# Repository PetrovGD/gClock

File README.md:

# gClock -- Simple and Reliable

### gClock is a simple alarm clock, powered by an ESP32C3. It features functions as:

* Setting an alarm
* Removing an alarm
* Setting minutes until the alarm
* more in future versions

## Bill of Materials (BOM)
 - 4pcs Cherry MX Switches
 - 4pcs Keycaps of your choice
 - 1pcs 3.3V buzzer
 - 1pcs Seeed Studio ESP32C3
 - 1pcs SSD1306 128x64 0.91inch display (I will source the screen myself and won't use the one in the Blare kit)
 - 1pcs 3D printed custom enclosure (containing a main part and a protective cover which is going to be glued to the main part)
 - 2pcs M3x8mm Screws
 - 4pcs M3x16mm Screws (For securing the top plate to the main part)
## Plans to upgrade
* Add a functionality for the user to choose a melody
* Add a snooze and stop alarm functions (now it just rings for set amount of seconds)
* Make a more futuristic design
## Screenshots of the project
### PCB design

### Schematic

### Top Part

### Bottom Part

### Main Menu

### Set alarm Menu

### Set minutes Menu

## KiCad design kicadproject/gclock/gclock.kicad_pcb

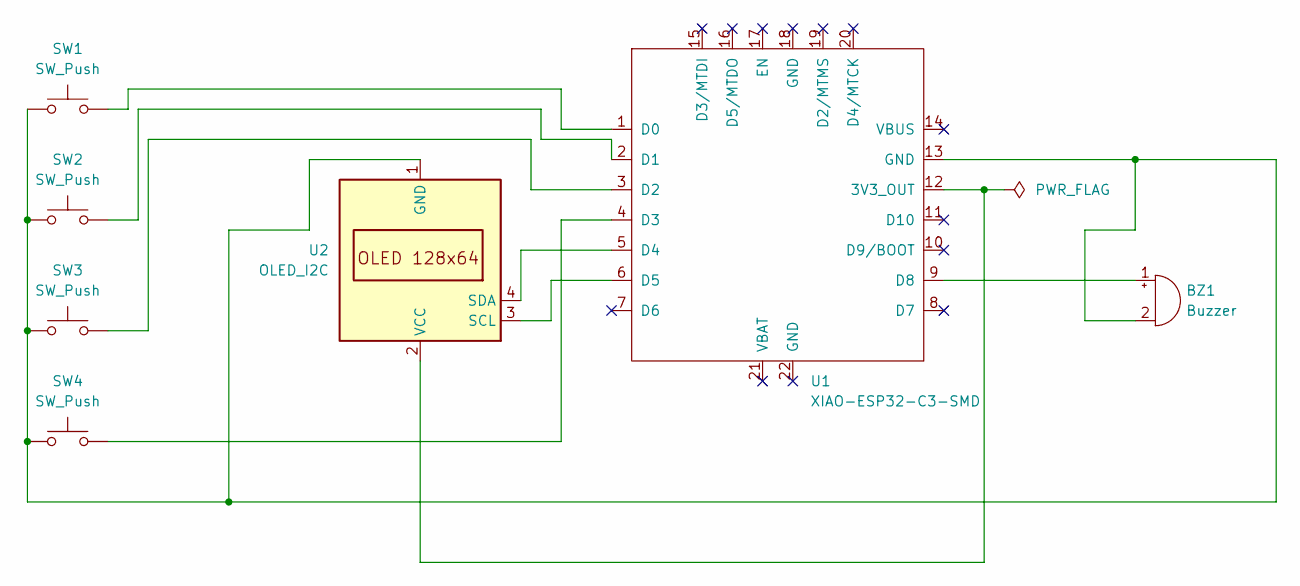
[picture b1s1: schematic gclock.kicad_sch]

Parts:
BZ1: Buzzer; Buzzer_12x9.5RM7.6
SW1, SW2, SW3, SW4: SW_Push; SW_Cherry_MX_1.00u_PCB
U1: XIAO-ESP32-C3-SMD; XIAO-ESP32-C3-DIP
U2: OLED_I2C; OLED_SSD1306_I2C_0.96

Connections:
unnamed: BZ1.1 (+), U1.9 (D8)
unnamed: BZ1.2 (-), SW1.1, SW2.1, SW3.1, SW4.1, U1.13 (GND), U2.1 (GND)
unnamed: U1.12 (3V3_OUT), U2.2 (VCC)
unnamed: SW1.2, U1.1 (D0)
unnamed: SW2.2, U1.2 (D1)
unnamed: SW3.2, U1.3 (D2)
unnamed: SW4.2, U1.4 (D3)
unnamed: U1.5 (D4), U2.4 (SDA)
unnamed: U1.6 (D5), U2.3 (SCL)

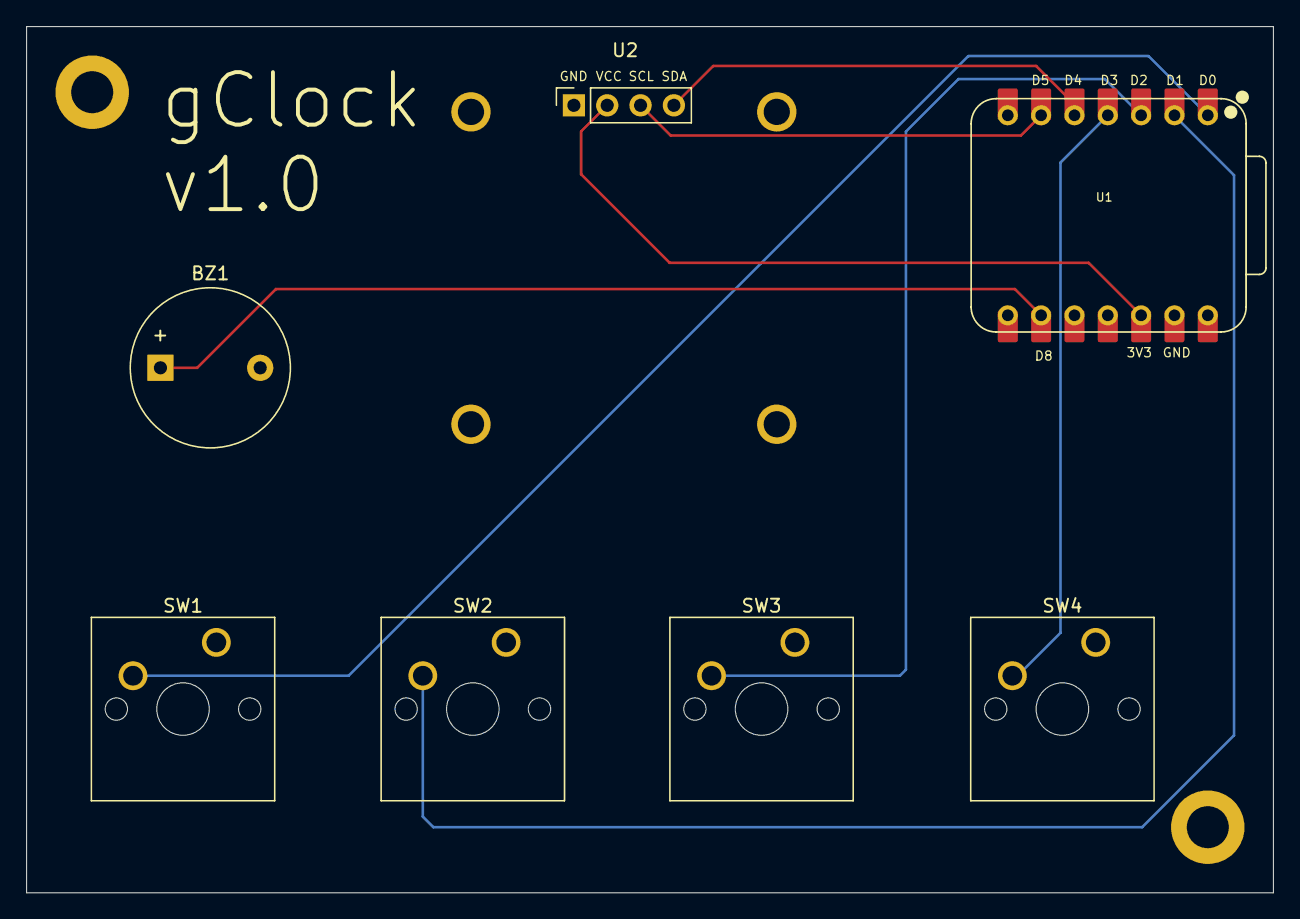
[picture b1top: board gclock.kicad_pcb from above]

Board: 2 copper layers, 95.0 x 66.0 mm, 7 parts (0 on the bottom side), 9 nets.
